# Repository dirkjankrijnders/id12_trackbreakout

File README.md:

ID 12 Track breakout
==================

Board for mounting a ID innovations ID-12 (or ID-20) RFID module under Märklin C or M rails. The board brings out the relevant pins to an RJ45 connector and a SIL header. It also has space for a local power regulator.

Couple of board are on order at oshpark: http://oshpark.com/shared_projects/GPSL45yw

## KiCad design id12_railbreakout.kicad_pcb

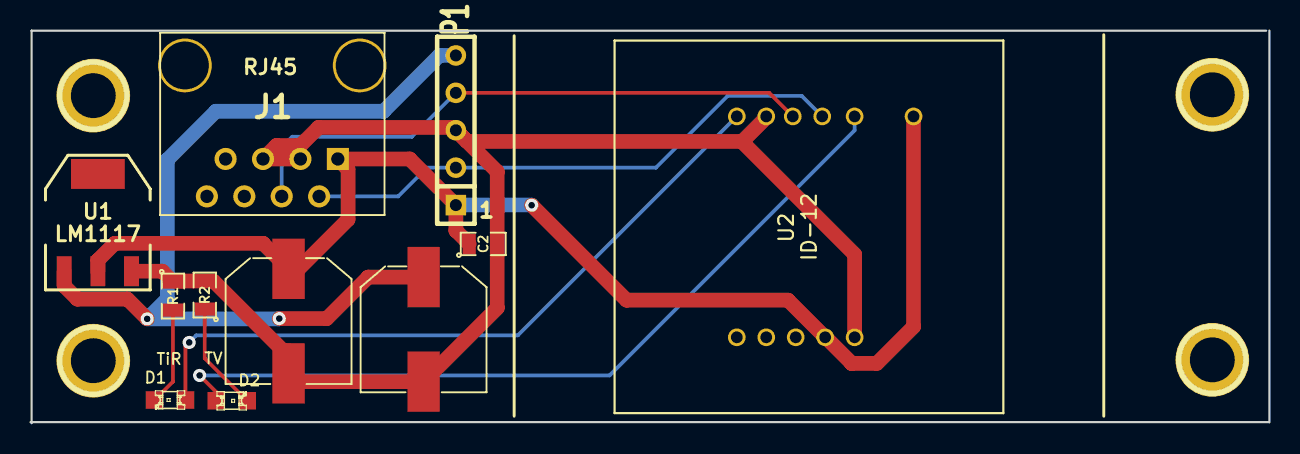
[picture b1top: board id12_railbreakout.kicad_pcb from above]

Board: 2 copper layers, 84.1 x 26.7 mm, 11 parts (0 on the bottom side), 9 nets.

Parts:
C1: C; c-smd-8mmx10.5mm
C2: C; SM0805
C3: CAPAPOL; c-smd-8mmx10.5mm
D1: TiR; LED-0805
D2: TV; LED-0805
J1: RJ45; RJ45_8
P1: CONN_5; SIL-5
R1, R2: R; SM0805
U1: LM1117; SOT223
U2: ID-12; RFID_ID12

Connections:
unnamed: D2.2, R2.1
unnamed: D1.2, R1.2
unnamed: D1.1, U2.6
unnamed: J1.2, P1.2, U2.8
unnamed: J1.4, P1.4, U2.9
unnamed: D2.1, U2.10
VAA: C1.1, P1.5, U1.1
VCC: C2.1, C3.1, J1.1, P1.1, U1.2, U2.2, U2.11
VSS: C1.2, C2.2, C3.2, J1.3, J1.5, P1.3, R1.1, R2.2, U1.3, U2.1, U2.7

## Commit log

2013-09-28 Small fixes and board layout
2013-09-28 Added images for documentation
